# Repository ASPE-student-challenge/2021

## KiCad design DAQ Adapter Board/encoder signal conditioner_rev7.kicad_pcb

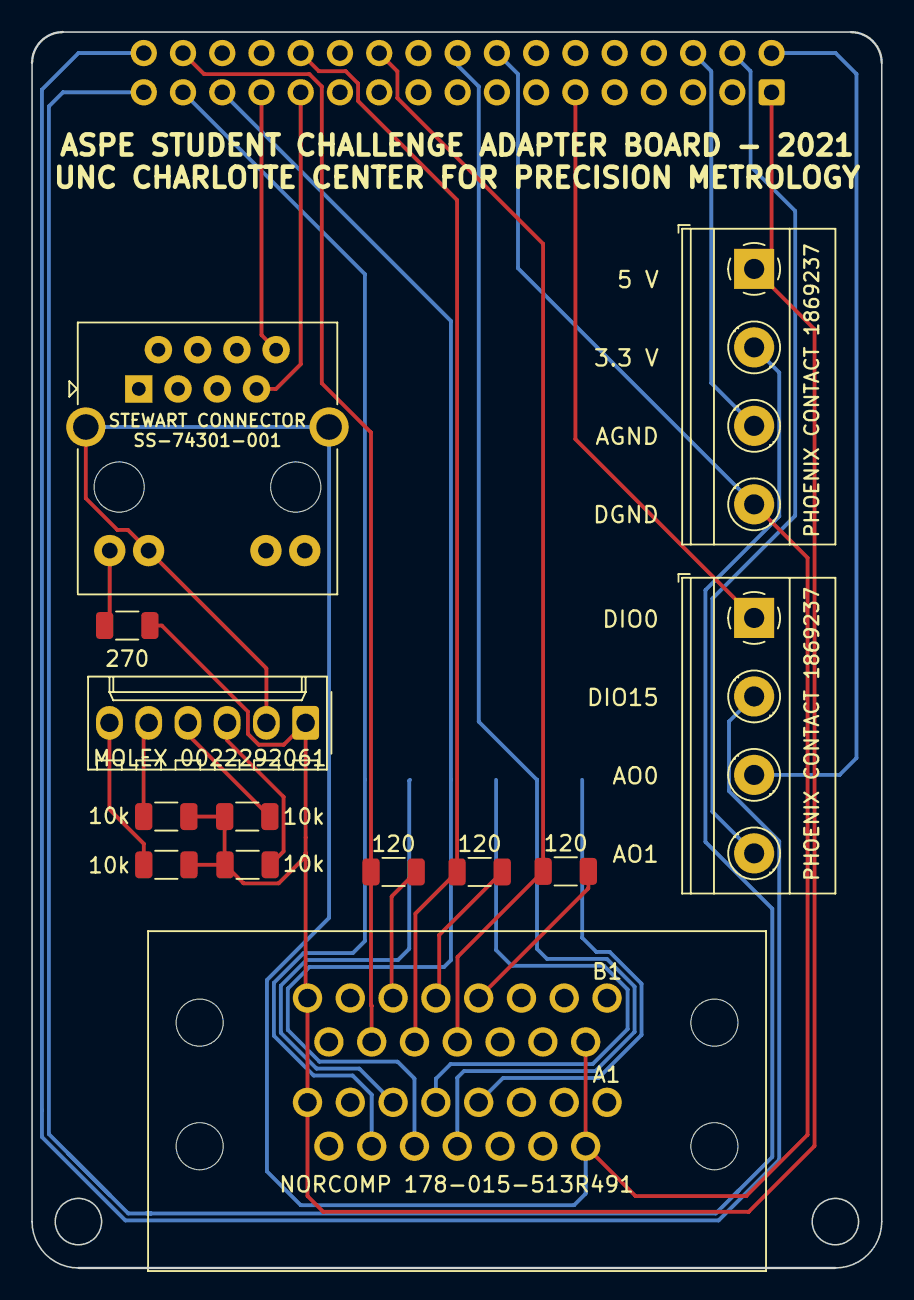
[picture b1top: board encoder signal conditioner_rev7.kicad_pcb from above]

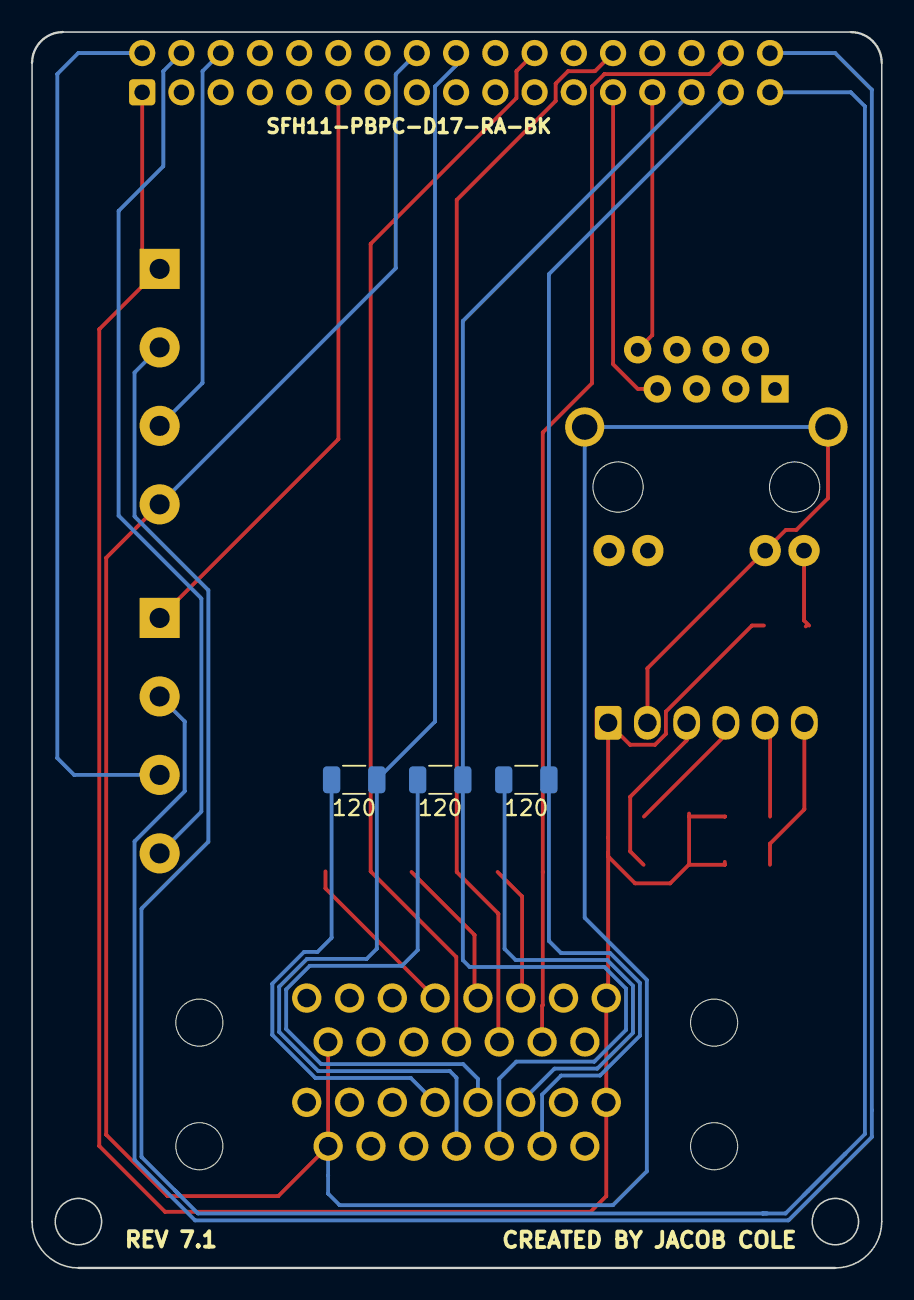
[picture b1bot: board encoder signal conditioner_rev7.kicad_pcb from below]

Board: 4 copper layers, 55.0 x 80.0 mm, 17 parts (4 on the bottom side), 33 nets.

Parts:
120, 120#2, 120#3, 120#4, 120#5, 120#6: Rload; R_1206_3216Metric
270: RLED; R_1206_3216Metric
J1: RJ45_LED_Shielded; RJ45_BEL_SS74301-00x_Vertical
J2: MOLEX 0022292061; Molex_KK-254_AE-6410-06A_1x06_P2.54mm_Vertical
J3: Conn_02x17_Odd_Even; IDC-Header_2x17_P2.54mm_Latch_Vertical
J4, J5: PHOENIX CONTACT 1869237; TerminalBlock_Phoenix_MKDS-1,5-4-5.08_1x04_P5.08mm_Horizont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
R7, R8, R9, R10: 10k; R_1206_3216Metric
U1: NORCOMP 178-015-513R491; DSUB-15_STACKED_Female_Horizontal

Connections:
/3.3V: J3.33, J4.2
/5V: 270.2, J2.1, J3.1, J4.1, R7.1, R8.1, R9.1, R10.1, U1.A8, U1.B8
/A0: 120#3.1, J3.18, U1.A12
/A1: 120.1, J3.31, U1.A14
/A2: 120#2.1, J3.29, U1.A13
/ADC_CLK: J1.3, J3.17
/ADC_READ: J1.1, J3.13
/ADC_WRITE: J1.2, J3.15
/AGND: J3.6, J4.3
/AI0: J2.3, J3.3, R10.2
/AI1: J2.4, J3.5, R9.2
/AI2: J2.5, J3.7, R8.2
/AI3: J2.6, J3.9, R7.2
/AO0: J3.2, J5.3
/AO1: J3.4, J5.4
/B0: 120#6.1, J3.22, U1.B12
/B1: 120#4.1, J3.32, U1.B14
/B2: 120#5.1, J3.26, U1.B13
/CS: J1.4, J3.19
/DAC1_WRITE: J1.6, J3.23
/DAC2_WRITE: J1.7, J3.25
/DAC3_WRITE: J1.8, J3.27
/DAC_CLK: J1.5, J3.21
/DGND: J1.11, J1.SH, J2.2, J3.16, J4.4, U1.A9, U1.B9
/DIO0: J3.11, J5.1
/DIO15: J3.34, J5.2
unnamed: 270.1, J1.12
unnamed: 120.2, U1.A6
unnamed: 120#2.2, U1.A5
unnamed: 120#3.2, U1.A4
unnamed: 120#4.2, U1.B6
unnamed: 120#5.2, U1.B5
unnamed: 120#6.2, U1.B4

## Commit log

2020-12-04 initial files
2020-12-11 Add files via upload
    added a change
2020-12-14 Folder
2020-12-14 Rename Diffraction Grating Test Setup.gdraw to Metrology/Diffraction Grating Test Setup.gdraw
2020-12-14 Rename Summary_SC2020_laser spectrum_Red_Green laser pointers.gslides to Metrology/Summary_SC2020_laser spectrum_Red_Green laser pointers.gslides
2020-12-18 I made a change.
    Added "A change" to the first bullet.
2020-12-18 I made a change
    Added "A change" to line 1
2021-01-16 myRIO essentials guide
2021-01-31 Current LV files as of 1 Feb 2021
2021-01-31 Current as of 1 Feb
2021-03-19 Updated LV files 20210319
2021-03-19 removing obsolete
2021-05-22 Adding updated files and temporary testing vis
2021-07-09 Latest XY slab air bearing design (by Mark K)
    "0502_assy XY stage slab arrangment" looks like it is the assembly file.
2021-07-11 init
